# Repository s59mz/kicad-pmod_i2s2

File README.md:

## Kicad project: PMOD I2S2 - Pmod module with I2S audo interface and two audio jacks.

3D view

Top view

Bottom view

Schematic:
[kicad-pmod_i2s2.pdf](kicad-pmod_i2s2.pdf)

BOM:
[kicad-pmod_i2s2.csv](kicad-pmod_i2s2.csv)

Gerbers:
[gerbers.zip](https://github.com/s59mz/kicad-pmod_i2s2/raw/main/gerbers.zip)

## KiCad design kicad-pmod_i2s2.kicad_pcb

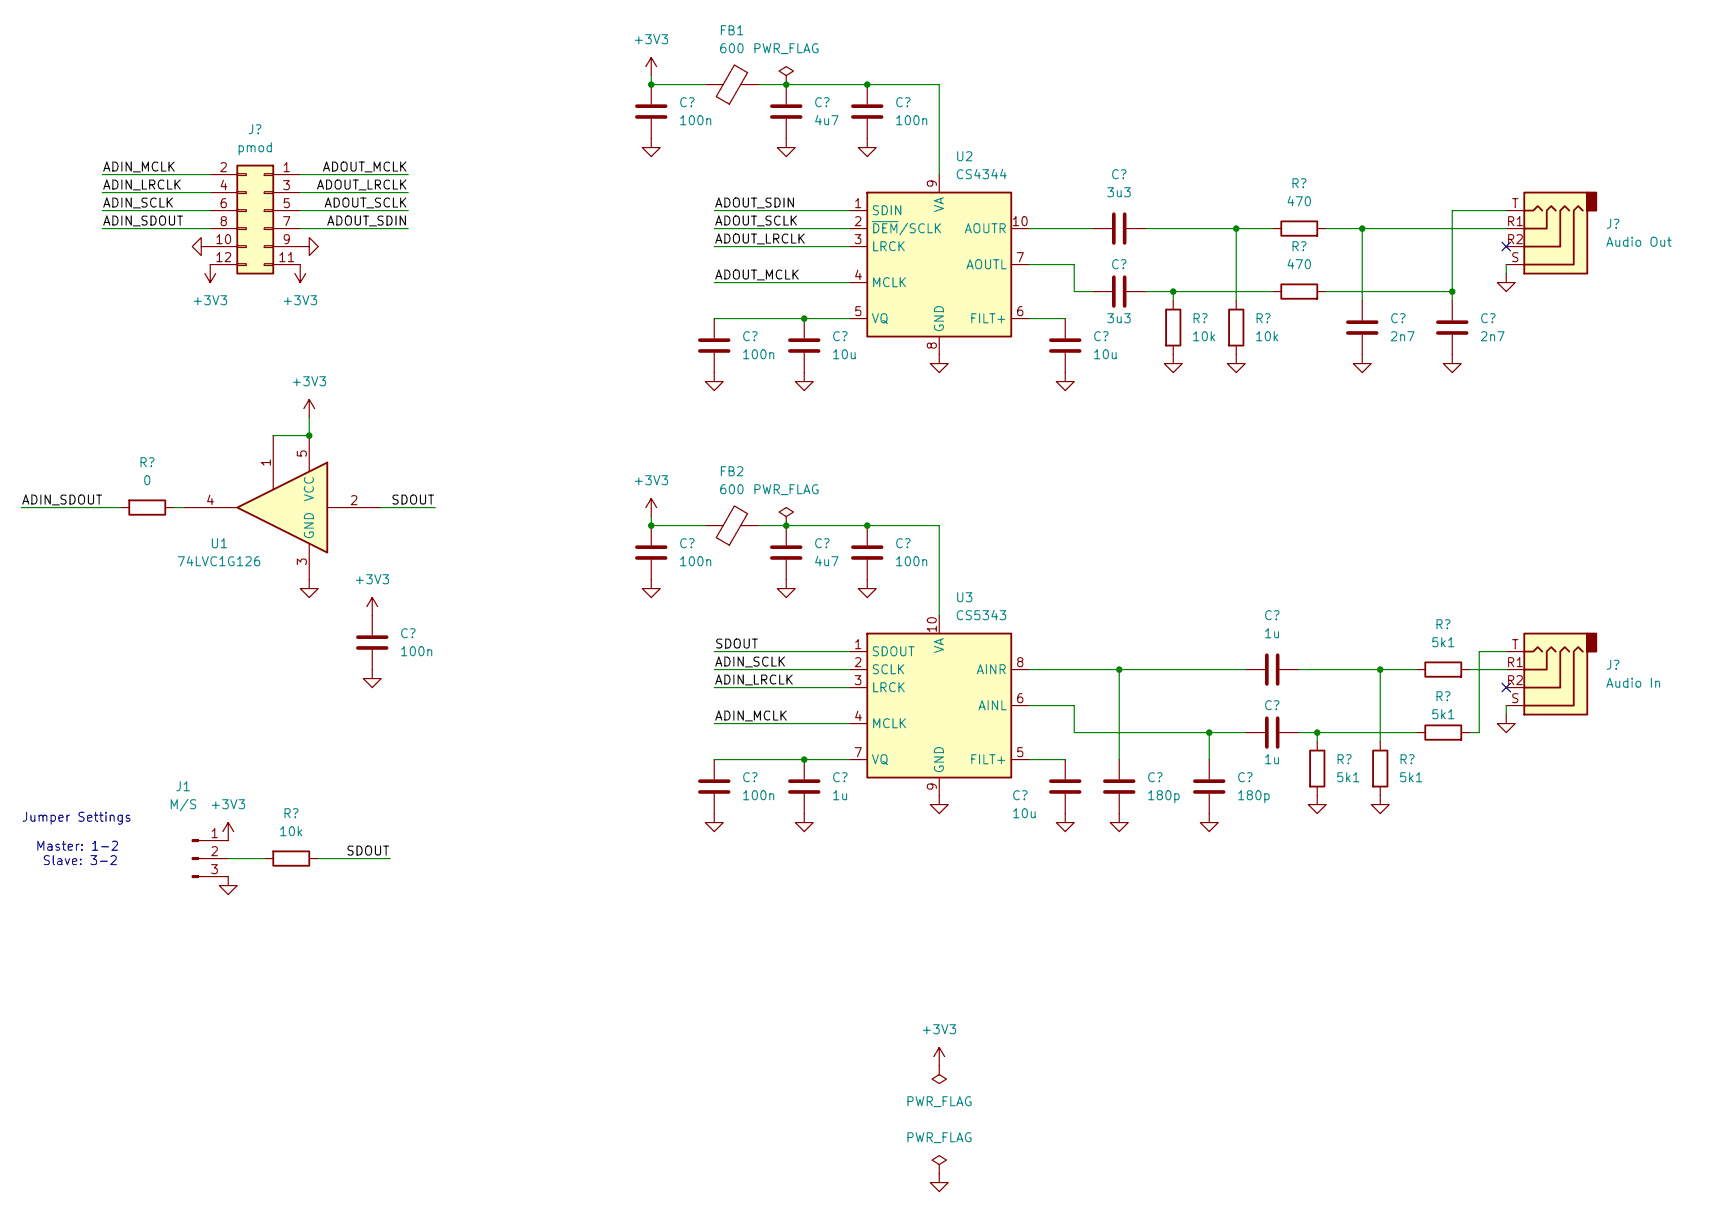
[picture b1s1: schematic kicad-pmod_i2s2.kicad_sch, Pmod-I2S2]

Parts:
C1, C2, C3, C4, C5, C10, C11: 100n; C_0603_1608Metric_Pad1.08x0.95mm_HandSolder
C6, C7: 4u7; C_0603_1608Metric_Pad1.08x0.95mm_HandSolder
C8, C12, C13: 10u; C_0603_1608Metric_Pad1.08x0.95mm_HandSolder
C9, C18, C19: 1u; C_0603_1608Metric_Pad1.08x0.95mm_HandSolder
C14, C15: 3u3; C_0603_1608Metric_Pad1.08x0.95mm_HandSolder
C16, C17: 180p; C_0603_1608Metric_Pad1.08x0.95mm_HandSolder
C20, C21: 2n7; C_0603_1608Metric_Pad1.08x0.95mm_HandSolder
FB1, FB2: 600; L_0603_1608Metric_Pad1.05x0.95mm_HandSolder
J1: M/S; PinHeader_1x03_P2.54mm_Vertical
J2: pmod; PinHeader_2x06_P2.54mm_Horizontal
J3: Audio Out; Jack_3.5mm_PJ320D_Horizontal
J4: Audio In; Jack_3.5mm_PJ320D_Horizontal
R1: 0; R_0603_1608Metric_Pad0.98x0.95mm_HandSolder
R2, R3, R4: 10k; R_0603_1608Metric_Pad0.98x0.95mm_HandSolder
R5, R6: 470; R_0603_1608Metric_Pad0.98x0.95mm_HandSolder
R7, R8, R9, R10: 5k1; R_0603_1608Metric_Pad0.98x0.95mm_HandSolder
U1: 74LVC1G126; SOT-23-5_HandSoldering
U2: CS4344; TSSOP-10_3x3mm_P0.5mm
U3: CS5343; TSSOP-10_3x3mm_P0.5mm

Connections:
+3V3: C1.1, C2.1, C3.1, FB1.1, FB2.1, J1.1, J2.11, J2.12, U1.1, U1.5 (VCC)
/ADIN_LRCLK: J2.4, U3.3 (LRCK)
/ADIN_MCLK: J2.2, U3.4 (MCLK)
/ADIN_SCLK: J2.6, U3.2 (SCLK)
/ADIN_SDOUT: J2.8, R1.2
/ADOUT_LRCLK: J2.3, U2.3 (LRCK)
/ADOUT_MCLK: J2.1, U2.4 (MCLK)
/ADOUT_SCLK: J2.5, U2.2 (~DEM/SCLK)
/ADOUT_SDIN: J2.7, U2.1 (SDIN)
/SDOUT: R2.1, U1.2, U3.1 (SDOUT)
GND: C1.2, C2.2, C3.2, C4.2, C5.2, C6.2, C7.2, C8.2, C9.2, C10.2, C11.2, C12.2, C13.2, C16.2, C17.2, C20.2, C21.2, J1.3, J2.9, J2.10, J3.S, J4.S, R3.2, R4.2, R7.2, R8.2, U1.3 (GND), U2.8 (GND), U3.9 (GND)
unnamed: C14.2, R4.1, R5.1
unnamed: C15.2, R3.1, R6.1
unnamed: C18.2, R8.1, R9.1
unnamed: C19.2, R7.1, R10.1
unnamed: C20.1, J3.R1, R5.2
unnamed: C21.1, J3.T, R6.2
unnamed: J1.2, R2.2
unnamed: J4.R1, R9.2
unnamed: J4.T, R10.2
unnamed: R1.1, U1.4
unnamed: C15.1, U2.7 (AOUTL)
unnamed: C14.1, U2.10 (AOUTR)
unnamed: C12.1, U2.6 (FILT+)
unnamed: C6.1, C10.1, FB1.2, U2.9 (VA)
unnamed: C4.1, C8.1, U2.5 (VQ)
unnamed: C17.1, C19.1, U3.6 (AINL)
unnamed: C16.1, C18.1, U3.8 (AINR)
unnamed: C13.1, U3.5 (FILT+)
unnamed: C7.1, C11.1, FB2.2, U3.10 (VA)
unnamed: C5.1, C9.1, U3.7 (VQ)

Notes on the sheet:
Jumper Settings Master: 1-2 Slave: 3-2

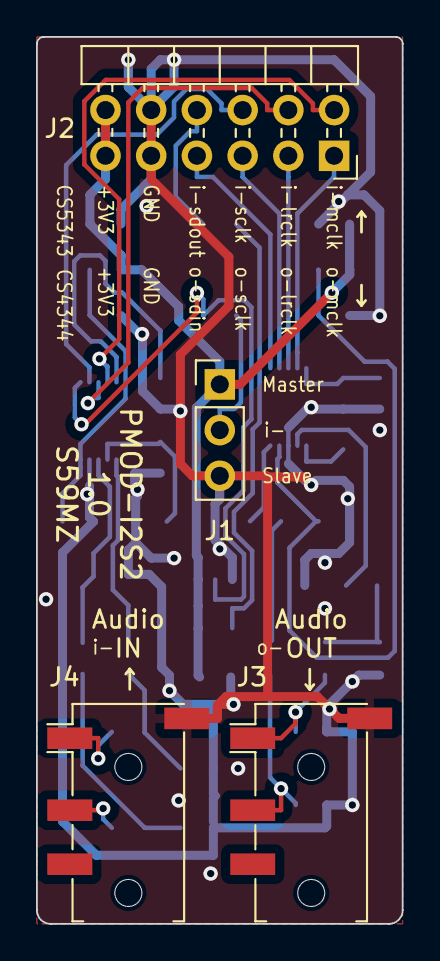
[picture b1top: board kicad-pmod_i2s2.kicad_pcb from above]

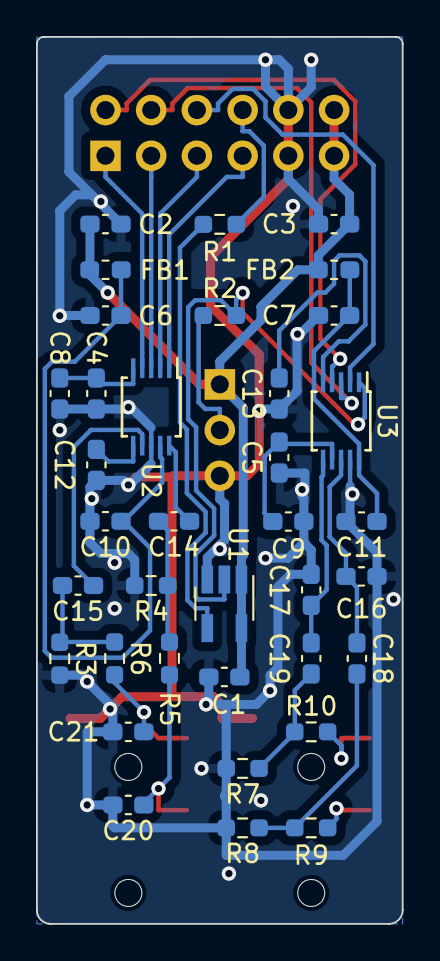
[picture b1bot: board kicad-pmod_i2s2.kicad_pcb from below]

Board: 2 copper layers, 20.3 x 49.3 mm, 40 parts (36 on the bottom side), 31 nets.

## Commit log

2023-11-15 made schematic and draft placement
2023-11-16 finished placement and refdes arragement
2023-11-16 1.0 - jlcpcb order
2023-12-04 update audio jack
2023-12-04 update ADC capacitors properties
2023-12-04 readme
